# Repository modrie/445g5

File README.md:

# 445g5
ECE445 Group 5 Facilitated Instrument Learning

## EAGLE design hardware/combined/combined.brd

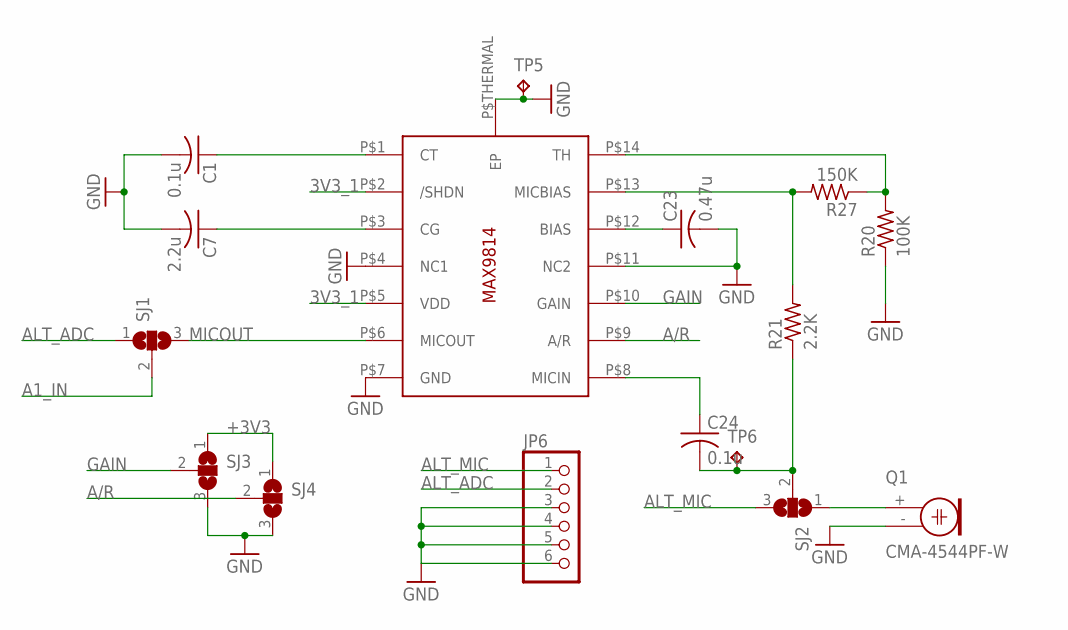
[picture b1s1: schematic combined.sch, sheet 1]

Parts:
C1, C24: 0.1u; C0603
C7: 2.2u; C0603
C23: 0.47u; C0603
JP6: PINHD-1X6; 1X06
Q1: CMA-4544PF-W; 9.7ELECTRET
R20: 100K; R0603
R21: 2.2K; R0603
R27: 150K; R0603
SJ1, SJ2, SJ3, SJ4: SJ2W; SJ_2
TP5, TP6: TPB1,27; B1,27
U$1: MAX9814TDFN14; TDFN14_3X3MM

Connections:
3V3_1: U$1.P$2 (/SHDN), U$1.P$5 (VDD)
+3V3: SJ3.1, SJ4.1; also elsewhere on the board
A1_IN: SJ1.2; also elsewhere on the board
A/R: SJ4.2, U$1.P$9 (A/R)
ALT_ADC: JP6.2, SJ1.1
ALT_MIC: JP6.1
GAIN: SJ3.2, U$1.P$10 (GAIN)
GND: C1.2, C7.2, C23.2, Q1.- (1), R20.1, SJ3.3, SJ4.3, TP5.TP, U$1.P$4 (NC1), U$1.P$7 (GND), U$1.P$11 (NC2), U$1.P$THERMAL (EP); also elsewhere on the board
INPUT: C24.2, R21.1, SJ2.2, TP6.TP
MICOUT: SJ1.3, U$1.P$6 (MICOUT)
unnamed: C24.1, U$1.P$8 (MICIN)
unnamed: C23.1, U$1.P$12 (BIAS)
unnamed: C1.1, U$1.P$1 (CT)
unnamed: C7.1, U$1.P$3 (CG)
unnamed: R20.2, R27.1, U$1.P$14 (TH)
unnamed: R21.2, R27.2, U$1.P$13 (MICBIAS)
unnamed: Q1.+ (2), SJ2.1
unnamed: JP6.3, JP6.4, JP6.5, JP6.6

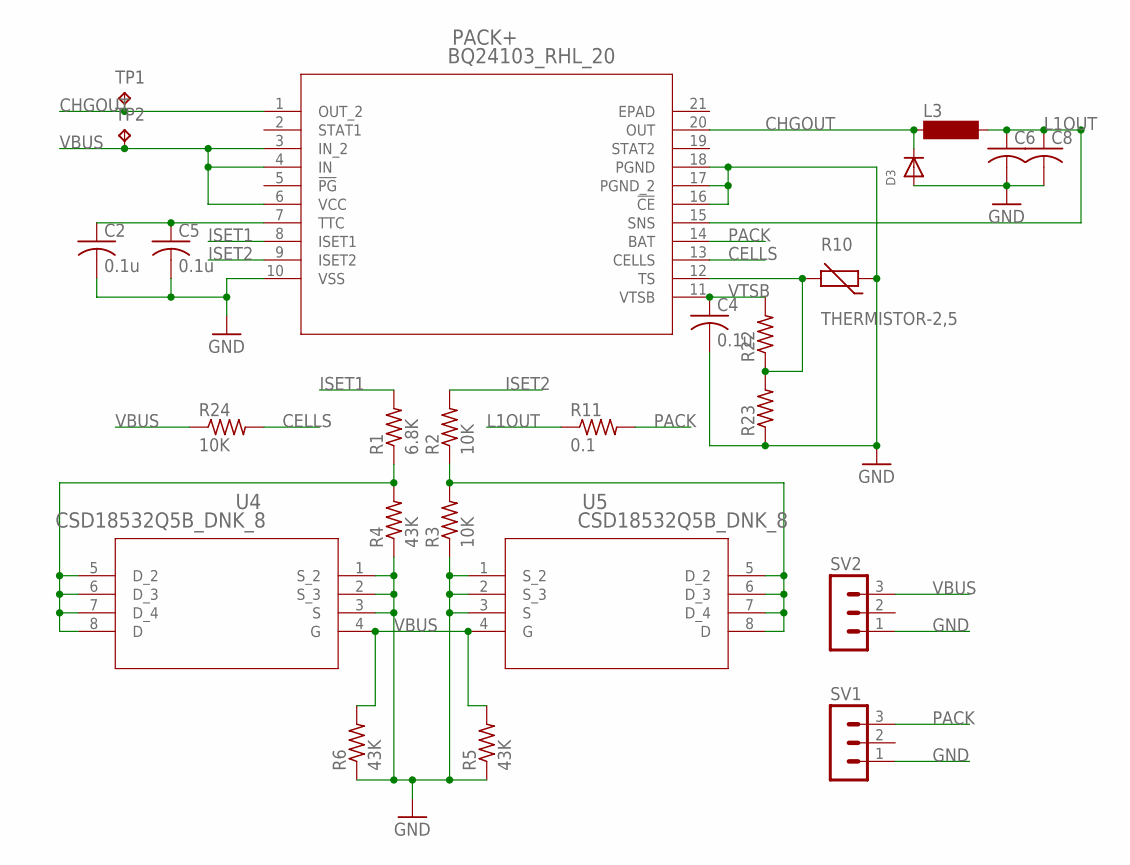
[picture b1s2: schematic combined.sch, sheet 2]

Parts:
C2, C4, C5: 0.1u; C0603
C6, C8: C-USC0805K; C0805K
D3: DIODESOD-323F; SOD-323F
L3: MS85
PACK+: BQ24103_RHL_20; RHL20_2P05X3P05
R1: 6.8K; R0603
R2, R3: 10K; R0603
R4, R5, R6: 43K; R0603
R10: THERMISTOR-2,5; RS-2,5
R11: 0.1; R0805
R22, R23: R-US_R0805; R0805
R24: 10K; R0805
SV1, SV2: MA03-1
TP1, TP2: TPB1,27; B1,27
U4, U5: CSD18532Q5B_DNK_8; DNK8

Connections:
CELLS: PACK+.13 (CELLS), R24.2
CHGOUT: D3.C, L3.1, PACK+.1 (OUT_2), PACK+.20 (OUT), TP1.TP
GND: C2.2, C4.2, C5.2, C6.2, C8.2, D3.A, PACK+.10 (VSS), PACK+.16 (!CE), PACK+.17 (PGND_2), PACK+.18 (PGND), R3.1, R4.1, R5.1, R6.1, R10.1, R23.1, SV1.1, SV2.1, U4.1 (S_2), U4.2 (S_3), U4.3 (S), U5.1 (S_2), U5.2 (S_3), U5.3 (S); also elsewhere on the board
ISET1: PACK+.8 (ISET1), R1.2
ISET2: PACK+.9 (ISET2), R2.2
L1OUT: C6.1, C8.1, L3.2, PACK+.15 (SNS), R11.1
unnamed: C2.1, C5.1, PACK+.7 (TTC)
unnamed: PACK+.12 (TS), R10.2, R22.1, R23.2
unnamed: R1.1, R4.2, U4.5 (D_2), U4.6 (D_3), U4.7 (D_4), U4.8 (D)
unnamed: R2.1, R3.2, U5.5 (D_2), U5.6 (D_3), U5.7 (D_4), U5.8 (D)
PACK: PACK+.14 (BAT), R11.2, SV1.3; also elsewhere on the board
VBUS: PACK+.3 (IN_2), PACK+.4 (IN), PACK+.6 (VCC), R5.2, R6.2, R24.1, SV2.3, TP2.TP, U4.4 (G), U5.4 (G); also elsewhere on the board
VTSB: C4.1, PACK+.11 (VTSB), R22.2

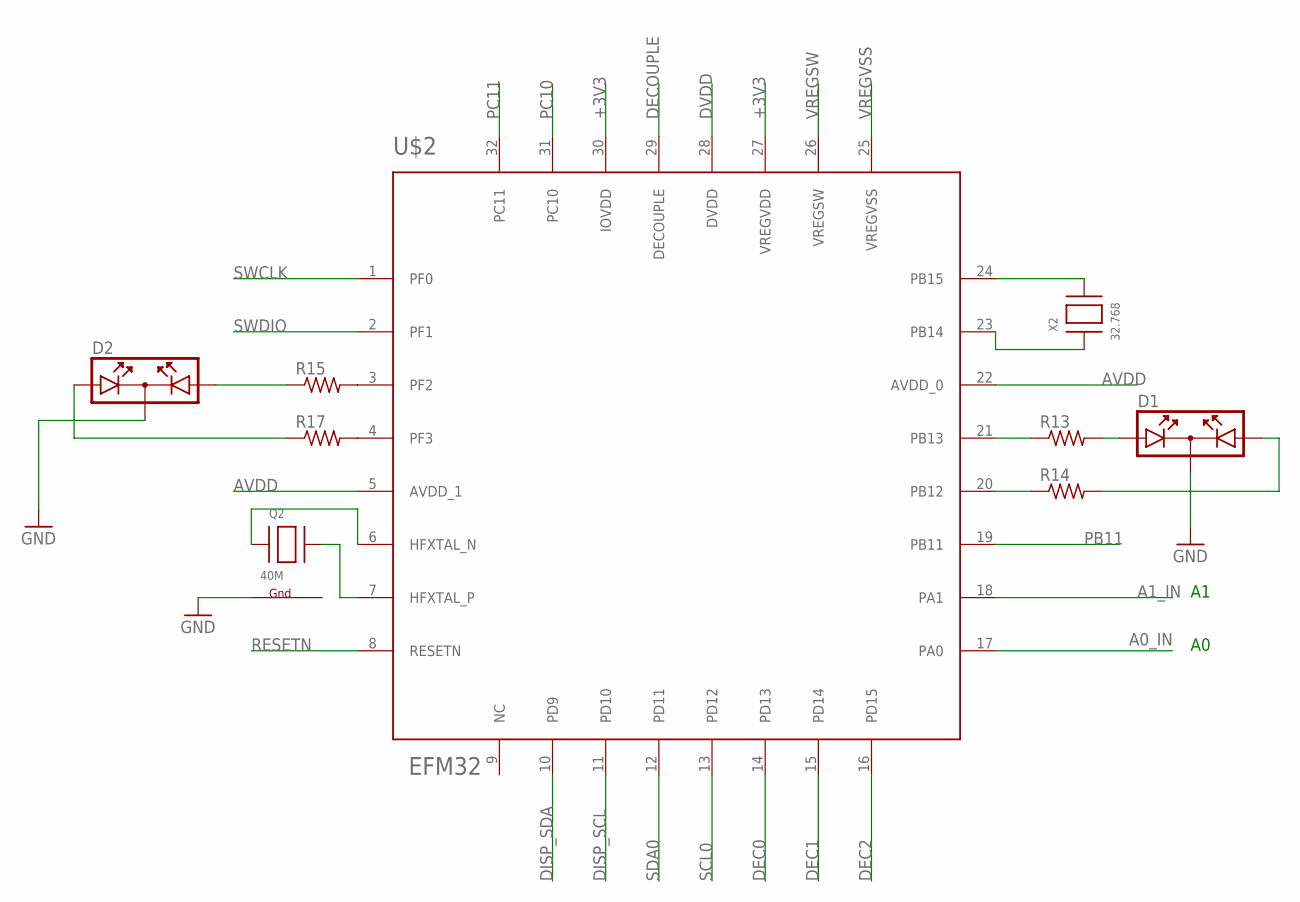
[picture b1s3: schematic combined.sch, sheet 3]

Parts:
D1, D2: DUOLED
Q2: 40M; NX3225
R13, R14, R15, R17: R-US_M0805; M0805
U$2: EFM32; QFN32
X2: 32.768; XTAL3215

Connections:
+3V3: U$2.27 (VREGVDD), U$2.30 (IOVDD); also elsewhere on the board
A0_IN: U$2.17 (PA0)
A1_IN: U$2.18 (PA1); also elsewhere on the board
AVDD: U$2.5 (AVDD_1), U$2.22 (AVDD_0); also elsewhere on the board
DEC0: U$2.14 (PD13); also elsewhere on the board
DEC1: U$2.15 (PD14); also elsewhere on the board
DEC2: U$2.16 (PD15); also elsewhere on the board
DECOUPLE: U$2.29 (DECOUPLE); also elsewhere on the board
DISP_SCL: U$2.11 (PD10); also elsewhere on the board
DISP_SDA: U$2.10 (PD9); also elsewhere on the board
DVDD: U$2.28 (DVDD); also elsewhere on the board
G2: Q2.2 (G2)
GND: D1.K, D2.K, Q2.4 (G1); also elsewhere on the board
unnamed: Q2.1 (X1), U$2.6 (HFXTAL_N)
unnamed: Q2.3 (X2), U$2.7 (HFXTAL_P)
unnamed: U$2.24 (PB15), X2.P$2
unnamed: U$2.23 (PB14), X2.P$1
unnamed: D1.A1, R13.2
unnamed: D1.A2, R14.2
unnamed: R15.2, U$2.3 (PF2)
unnamed: D2.A2, R15.1
unnamed: R17.2, U$2.4 (PF3)
unnamed: D2.A1, R17.1
unnamed: R14.1, U$2.20 (PB12)
unnamed: R13.1, U$2.21 (PB13)
PB11: U$2.19 (PB11); also elsewhere on the board
PC10: U$2.31 (PC10); also elsewhere on the board
PC11: U$2.32 (PC11); also elsewhere on the board
RESETN: U$2.8 (RESETN)
SCL0: U$2.13 (PD12); also elsewhere on the board
SDA0: U$2.12 (PD11); also elsewhere on the board
SWCLK: U$2.1 (PF0); also elsewhere on the board
SWDIO: U$2.2 (PF1); also elsewhere on the board
VREGSW: U$2.26 (VREGSW); also elsewhere on the board
VREGVSS: U$2.25 (VREGVSS)

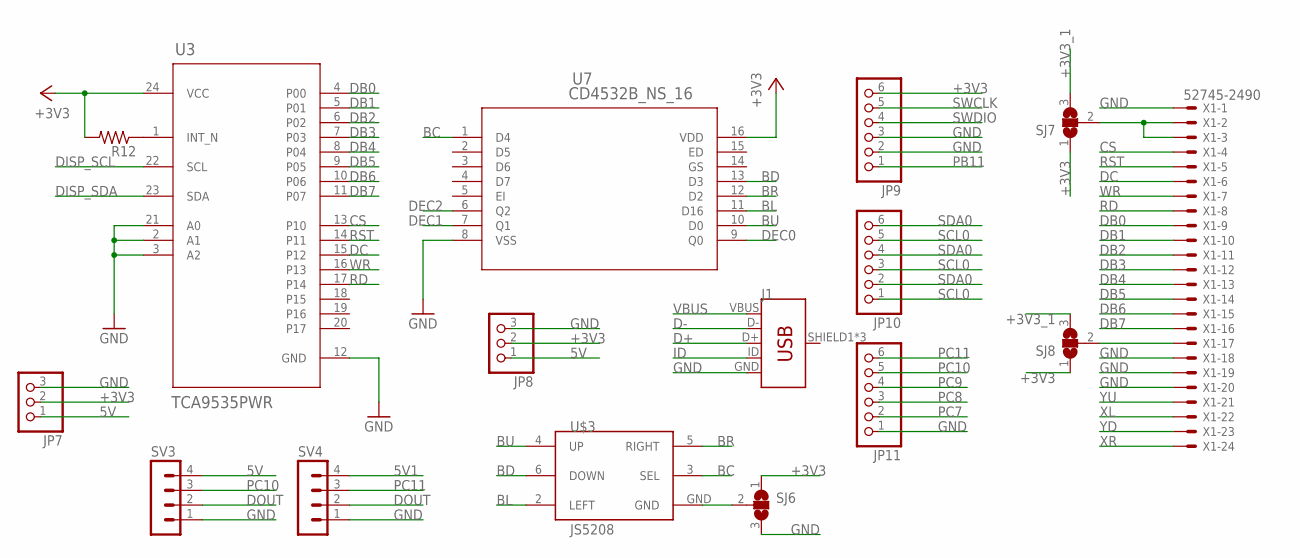
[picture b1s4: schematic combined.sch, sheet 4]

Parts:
J1: USB_MICRO-B_FEMALE-SMT; USB-B-MICRO-SMD
JP7, JP8: PINHD-1X3; 1X03
JP9, JP10, JP11: PINHD-1X6; 1X06
R12: R-US_M0805; M0805
SJ6, SJ7, SJ8: SJ2W; SJ_2
SV3, SV4: MA04-1
U3: TCA9535PWR; PW0024A_N
U7: CD4532B_NS_16; NS16
U$3: JS5208
X1: 52745-2490

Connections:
5V: JP7.1, JP8.1, SV3.4; also elsewhere on the board
5V1: SV4.4; also elsewhere on the board
+3V3: JP7.2, JP8.2, JP9.6, R12.2, SJ6.1, SJ7.1, SJ8.1, U3.24 (VCC), U7.16 (VDD); also elsewhere on the board
+3V3_1: SJ7.3, SJ8.3; also elsewhere on the board
BC: U7.1 (D4), U$3.3 (SEL)
BD: U7.13 (D3), U$3.6 (DOWN)
BL: U7.11 (D16), U$3.2 (LEFT)
BR: U7.12 (D2), U$3.5 (RIGHT)
BU: U7.10 (D0), U$3.4 (UP)
CS: U3.13 (P10), X1.4
D+: J1.D+
D-: J1.D-
DB0: U3.4 (P00), X1.9
DB1: U3.5 (P01), X1.10
DB2: U3.6 (P02), X1.11
DB3: U3.7 (P03), X1.12
DB4: U3.8 (P04), X1.13
DB5: U3.9 (P05), X1.14
DB6: U3.10 (P06), X1.15
DB7: U3.11 (P07), X1.16
DC: U3.15 (P12), X1.6
DEC0: U7.9 (Q0); also elsewhere on the board
DEC1: U7.7 (Q1); also elsewhere on the board
DEC2: U7.6 (Q2); also elsewhere on the board
DISP_SCL: U3.22 (SCL); also elsewhere on the board
DISP_SDA: U3.23 (SDA); also elsewhere on the board
DOUT: SV3.2, SV4.2
GND: J1.GND, JP7.3, JP8.3, JP9.2, JP9.3, JP11.1, SJ6.3, SV3.1, SV4.1, U3.2 (A1), U3.3 (A2), U3.12 (GND), U3.21 (A0), U7.8 (VSS), X1.1, X1.18, X1.19, X1.20; also elsewhere on the board
ID: J1.ID
unnamed: SJ7.2, X1.2, X1.3
unnamed: SJ8.2, X1.17
unnamed: SJ6.2, U$3.GND
unnamed: R12.1, U3.1 (INT_N)
PB11: JP9.1; also elsewhere on the board
PC7: JP11.2
PC8: JP11.3
PC9: JP11.4
PC10: JP11.5, SV3.3; also elsewhere on the board
PC11: JP11.6, SV4.3; also elsewhere on the board
RD: U3.17 (P14), X1.8
RST: U3.14 (P11), X1.5
SCL0: JP10.1, JP10.3, JP10.5; also elsewhere on the board
SDA0: JP10.2, JP10.4, JP10.6; also elsewhere on the board
SWCLK: JP9.5; also elsewhere on the board
SWDIO: JP9.4; also elsewhere on the board
VBUS: J1.VBUS; also elsewhere on the board
WR: U3.16 (P13), X1.7
XL: X1.22
XR: X1.24
YD: X1.23
YU: X1.21

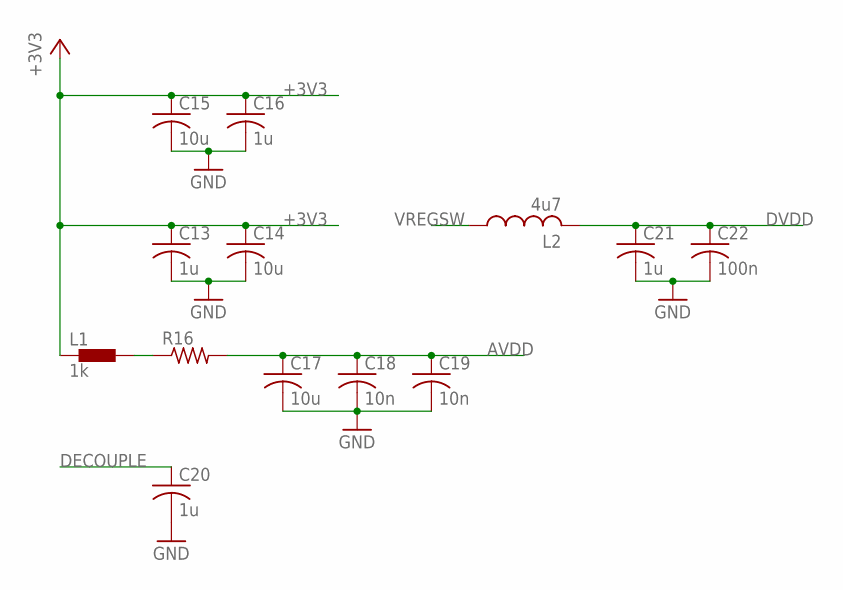
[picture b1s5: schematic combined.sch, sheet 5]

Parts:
C13, C16, C20, C21: 1u; C0805
C14, C15, C17: 10u; C0805
C18, C19: 10n; C0805
C22: 100n; C0805
L1: 1k; 0402
L2: 4u7; L3225P
R16: R-US_R0603; R0603

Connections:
+3V3: C13.1, C14.1, C15.1, C16.1, L1.1; also elsewhere on the board
AVDD: C17.1, C18.1, C19.1, R16.2; also elsewhere on the board
DECOUPLE: C20.1; also elsewhere on the board
DVDD: C21.1, C22.1, L2.2; also elsewhere on the board
GND: C13.2, C14.2, C15.2, C16.2, C17.2, C18.2, C19.2, C20.2, C21.2, C22.2; also elsewhere on the board
unnamed: L1.2, R16.1
VREGSW: L2.1; also elsewhere on the board

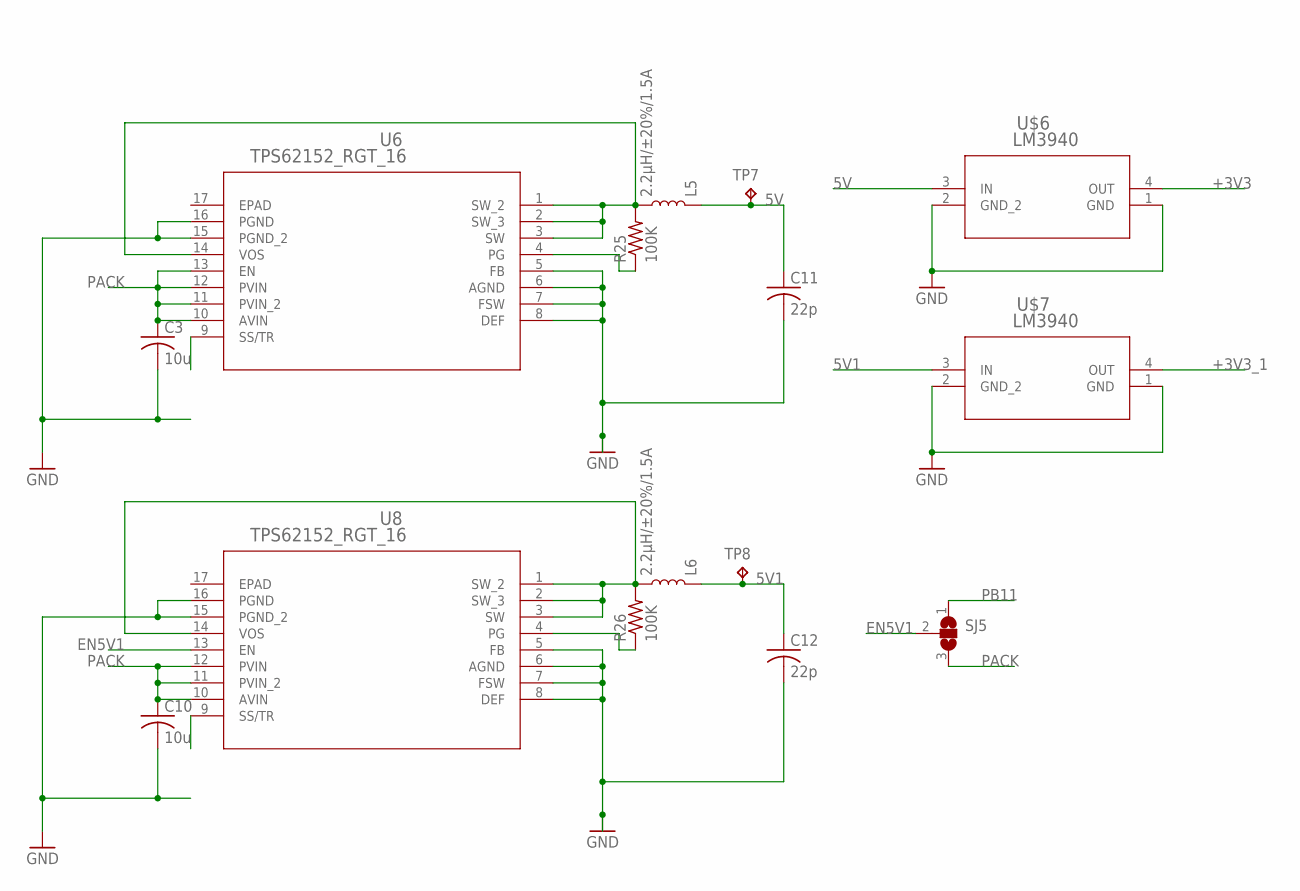
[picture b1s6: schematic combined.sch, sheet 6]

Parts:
C3, C10: 10u; C0603K
C11, C12: 22p; C0603K
L5, L6: 2.2µH/±20%/1.5A; INDUCTOR_2.2UH
R25, R26: 100K; R0603
SJ5: SJ2W; SJ_2
TP7, TP8: TPB1,27; B1,27
U6, U8: TPS62152_RGT_16; RGT16_1P7X1P7
U$6, U$7: LM3940; MP04A

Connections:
5V: C11.1, L5.P$1 (1), TP7.TP, U$6.3 (IN); also elsewhere on the board
5V1: C12.1, L6.P$1 (1), TP8.TP, U$7.3 (IN); also elsewhere on the board
+3V3: U$6.4 (OUT); also elsewhere on the board
+3V3_1: U$7.4 (OUT); also elsewhere on the board
EN5V1: SJ5.2, U8.13 (EN)
GND: C3.2, C10.2, C11.2, C12.2, U6.5 (FB), U6.6 (AGND), U6.7 (FSW), U6.8 (DEF), U6.15 (PGND_2), U6.16 (PGND), U8.5 (FB), U8.6 (AGND), U8.7 (FSW), U8.8 (DEF), U8.15 (PGND_2), U8.16 (PGND), U$6.1 (GND), U$6.2 (GND_2), U$7.1 (GND), U$7.2 (GND_2); also elsewhere on the board
unnamed: L5.P$2 (2), R25.2, U6.1 (SW_2), U6.2 (SW_3), U6.3 (SW), U6.14 (VOS)
unnamed: R25.1, U6.4 (PG)
unnamed: L6.P$2 (2), R26.2, U8.1 (SW_2), U8.2 (SW_3), U8.3 (SW), U8.14 (VOS)
unnamed: R26.1, U8.4 (PG)
PACK: C3.1, C10.1, SJ5.3, U6.10 (AVIN), U6.11 (PVIN_2), U6.12 (PVIN), U6.13 (EN), U8.10 (AVIN), U8.11 (PVIN_2), U8.12 (PVIN); also elsewhere on the board
PB11: SJ5.1; also elsewhere on the board

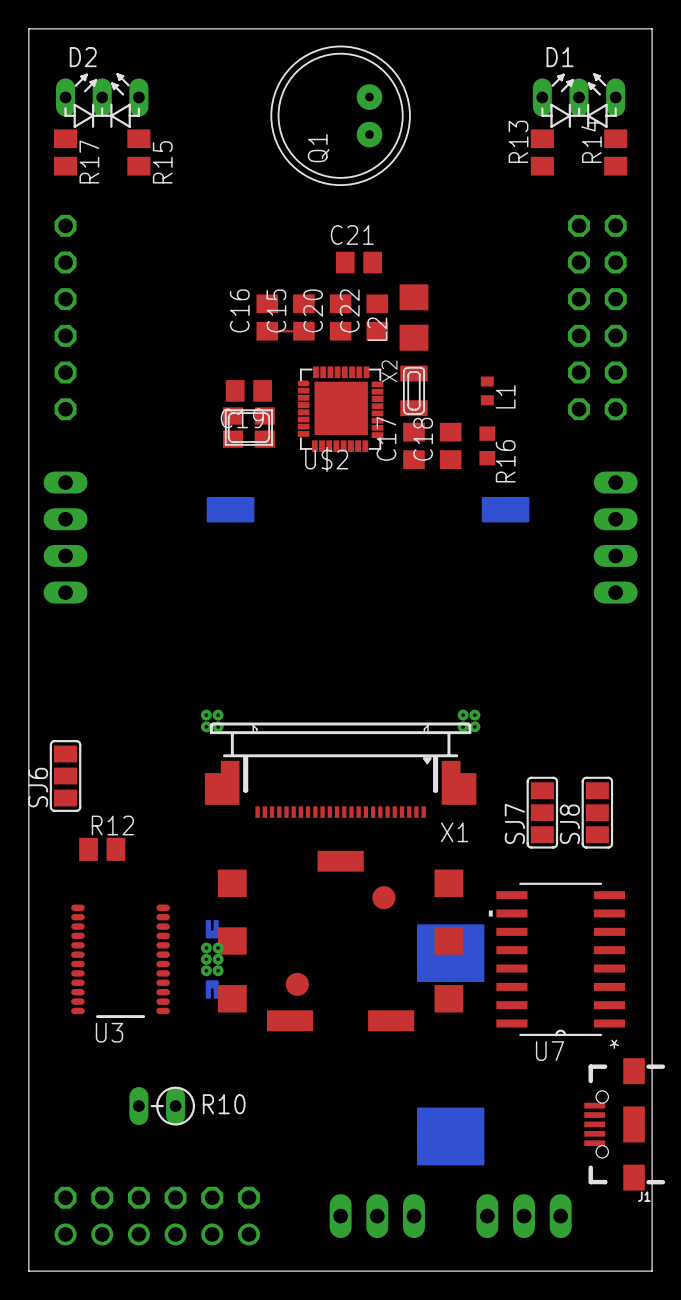
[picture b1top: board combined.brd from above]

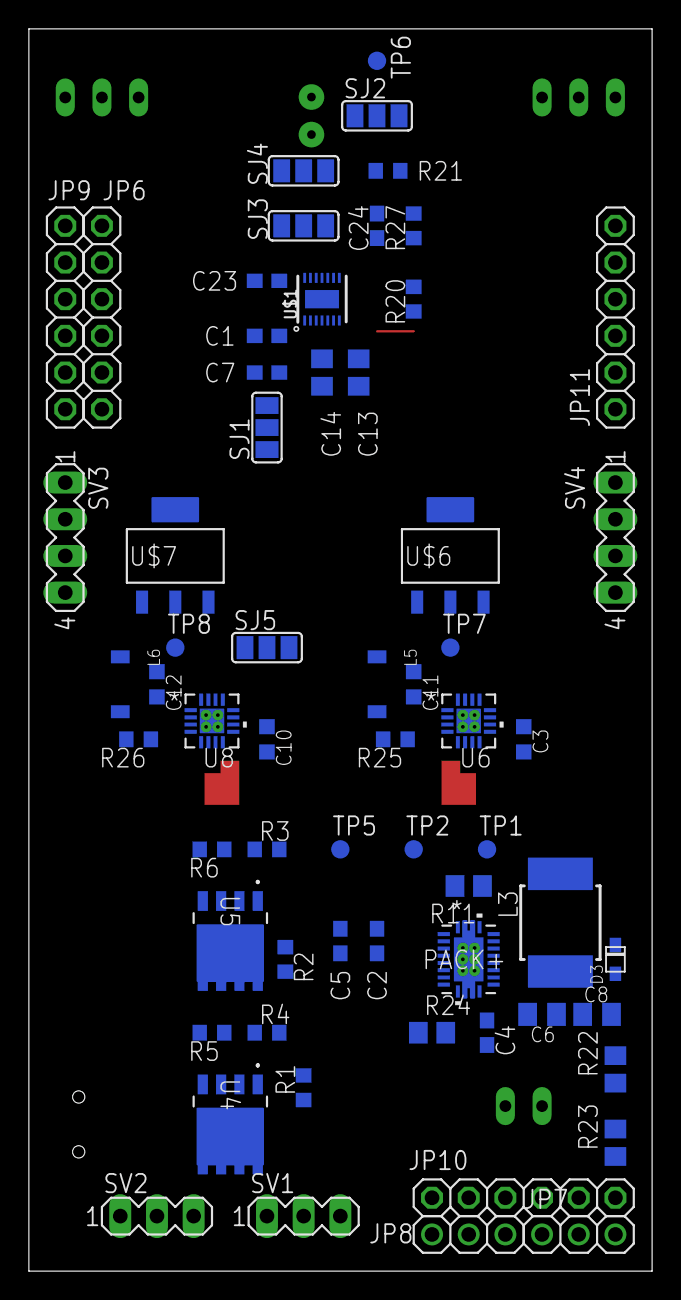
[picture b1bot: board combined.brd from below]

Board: 2 copper layers, 43.2 x 86.0 mm, 94 parts (63 on the bottom side), 89 nets.

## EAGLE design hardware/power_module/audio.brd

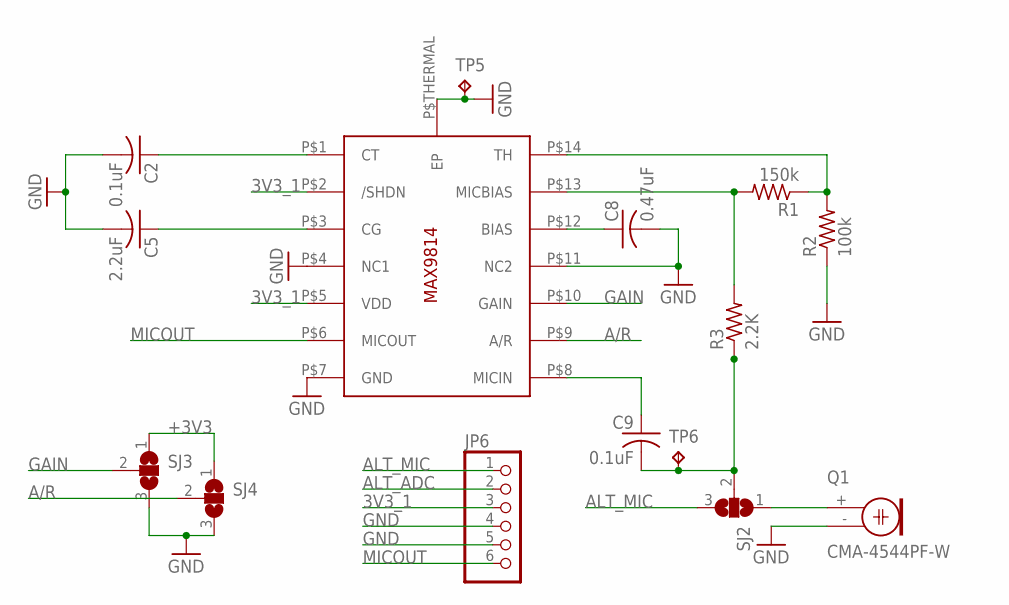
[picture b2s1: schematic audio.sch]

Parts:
C2, C9: 0.1uF; C0805K
C5: 2.2uF; C0805K
C8: 0.47uF; C0805K
JP6: PINHD-1X6; 1X06
Q1: CMA-4544PF-W; 9.7ELECTRET
R1: 150k; R0805
R2: 100k; R0805
R3: 2.2K; R0805
SJ2, SJ3, SJ4: SJ2W; SJ_2
TP5, TP6: TPB1,27; B1,27
U$1: MAX9814TDFN14; TDFN14_3X3MM

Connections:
3V3_1: JP6.3, U$1.P$2 (/SHDN), U$1.P$5 (VDD)
+3V3: SJ3.1, SJ4.1
A/R: SJ4.2, U$1.P$9 (A/R)
ALT_ADC: JP6.2
ALT_MIC: JP6.1, SJ2.3
GAIN: SJ3.2, U$1.P$10 (GAIN)
GND: C2.2, C5.2, C8.2, JP6.4, JP6.5, Q1.- (1), R2.1, SJ3.3, SJ4.3, TP5.TP, U$1.P$4 (NC1), U$1.P$7 (GND), U$1.P$11 (NC2), U$1.P$THERMAL (EP)
INPUT: C9.2, R3.1, SJ2.2, TP6.TP
MICOUT: JP6.6, U$1.P$6 (MICOUT)
unnamed: C9.1, U$1.P$8 (MICIN)
unnamed: C8.1, U$1.P$12 (BIAS)
unnamed: C2.1, U$1.P$1 (CT)
unnamed: C5.1, U$1.P$3 (CG)
unnamed: R1.1, R2.2, U$1.P$14 (TH)
unnamed: R1.2, R3.2, U$1.P$13 (MICBIAS)
unnamed: Q1.+ (2), SJ2.1

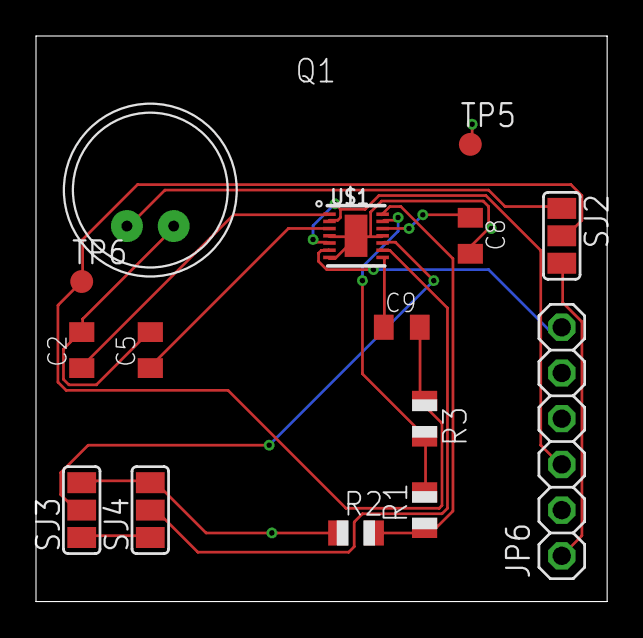
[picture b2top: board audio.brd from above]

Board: 2 copper layers, 31.7 x 31.4 mm, 15 parts (0 on the bottom side), 15 nets.

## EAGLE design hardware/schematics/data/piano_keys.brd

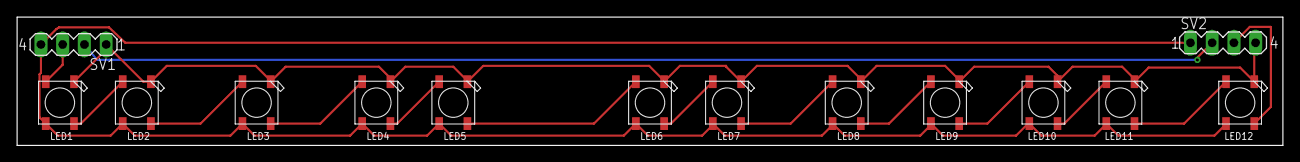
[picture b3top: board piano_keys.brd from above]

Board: 2 copper layers, 148.0 x 15.0 mm, 14 parts (0 on the bottom side), 16 nets.

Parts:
LED1, LED2, LED3, LED4, LED5, LED6, LED7, LED8, LED9, LED10, LED11, LED12: WS2812B5050; WS2812B
SV1, SV2: MA04-1

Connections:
5V1: LED1.1-VDD, LED2.1-VDD, LED3.1-VDD, LED4.1-VDD, LED5.1-VDD, LED6.1-VDD, LED7.1-VDD, LED8.1-VDD, LED9.1-VDD, LED10.1-VDD, LED11.1-VDD, LED12.1-VDD, SV1.4, SV2.1
DIN: LED1.4-DIN, SV1.3
DIN_1: SV1.2, SV2.2
DOUT_1: LED12.2-DOUT, SV2.3
GND: LED1.3-GND, LED2.3-GND, LED3.3-GND, LED4.3-GND, LED5.3-GND, LED6.3-GND, LED7.3-GND, LED8.3-GND, LED9.3-GND, LED10.3-GND, LED11.3-GND, LED12.3-GND, SV1.1, SV2.4
unnamed: LED3.2-DOUT, LED4.4-DIN
unnamed: LED4.2-DOUT, LED5.4-DIN
unnamed: LED5.2-DOUT, LED6.4-DIN
unnamed: LED6.2-DOUT, LED7.4-DIN
unnamed: LED7.2-DOUT, LED8.4-DIN
unnamed: LED8.2-DOUT, LED9.4-DIN
unnamed: LED9.2-DOUT, LED10.4-DIN
unnamed: LED10.2-DOUT, LED11.4-DIN
unnamed: LED11.2-DOUT, LED12.4-DIN
unnamed: LED1.2-DOUT, LED2.4-DIN
unnamed: LED2.2-DOUT, LED3.4-DIN

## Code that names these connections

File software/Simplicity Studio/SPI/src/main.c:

/**************************************************************************//**
 * @main_series1.c
 * @brief Demonstrates USART1 as SPI master.
 * @version 0.0.1
 ******************************************************************************
 * @section License
 * <b>Copyright 2015 Silicon Labs, Inc. http://www.silabs.com</b>
 *******************************************************************************
 *
 * This file is licensed under the Silabs License Agreement. See the file
 * "Silabs_License_Agreement.txt" for details. Before using this software for
 * any purpose, you must agree to the terms of that agreement.
 *
 ******************************************************************************/

#include "em_device.h"
#include "em_chip.h"
#include "em_cmu.h"
#include "em_gpio.h"
#include "em_usart.h"
#include "retargetswo.h"
#include <stdint.h>
#include <stdio.h>


#define NUM_LEDS 		 24
const uint8_t two_bits_to_SPI[4] = {0x88 ,0xE8, 0x8E,0xEE};
// Lookup table for bytes
// Index - 0b(MSB)(LSB)
// MSB is sent to line first, so the values corresponding to the index are flipped

// e.g  Sending 0b10
//			0 -> 0b1000 = 0x8
//			1 -> 0b1110 = 0xE
// 		Index is 2 so lookup table returns 0x8E in correct order



volatile uint32_t msTicks; /* counts 1ms timeTicks */

void Delay(uint32_t dlyTicks);

/***************************************************************************//**
 * @brief SysTick_Handler
 * Interrupt Service Routine for system tick counter
 ******************************************************************************/
void SysTick_Handler(void)
{
  msTicks++;       /* increment counter necessary in Delay()*/
}

/***************************************************************************//**
 * @brief Delays number of msTick Systicks (typically 1 ms)
 * @param dlyTicks Number of ticks to delay
 ******************************************************************************/
void Delay(uint32_t dlyTicks)
{
  uint32_t curTicks;

  curTicks = msTicks;
  while ((msTicks - curTicks) < dlyTicks) ;
}


/**************************************************************************//**
 * @brief Initialize USART1
 *****************************************************************************/
void initUSART1 (void)
{
	CMU_ClockEnable(cmuClock_HFPER, true);
	CMU_ClockEnable(cmuClock_GPIO, true);
	CMU_ClockEnable(cmuClock_USART1, true);

	// Start with default config, then modify as necessary
	USART_InitSync_TypeDef config = USART_INITSYNC_DEFAULT;
	config.master       = true;            // master mode
	config.baudrate     = 3333333; //5000000;         // CLK freq is 1 MHz
	config.autoCsEnable = true;            // CS pin controlled by hardware, not firmware
	config.clockMode    = usartClockMode0; // clock idle low, sample on rising/first edge
	config.msbf         = true;            // send MSB first
    USART_InitSync(USART1, &config);

    // Set USART pin locations
    USART1->ROUTELOC0 = (USART_ROUTELOC0_CLKLOC_LOC15) | // US1_CLK† † † †on location 15 = PD9
                        (USART_ROUTELOC0_CSLOC_LOC15)  | // US1_CS† † † † on location 15 = PD10
                        (USART_ROUTELOC0_TXLOC_LOC15)  | // US1_TX (MOSI) on location 15 = PC10
                        (USART_ROUTELOC0_RXLOC_LOC15);   // US1_RX (MISO) on location 15 = PC11

    // Enable USART pins
    USART1->ROUTEPEN = USART_ROUTEPEN_CLKPEN | USART_ROUTEPEN_CSPEN | USART_ROUTEPEN_TXPEN | USART_ROUTEPEN_RXPEN;

    // Configure GPIO mode
    GPIO_PinModeSet(gpioPortD, 9, gpioModePushPull, 1); // US1_CLK is push pull
    GPIO_PinModeSet(gpioPortD, 10, gpioModePushPull, 1); // US1_CS is push pull
    GPIO_PinModeSet(gpioPortC, 10, gpioModePushPull, 1); // US1_TX (MOSI) is push pull
    GPIO_PinModeSet(gpioPortC, 11, gpioModeInput, 1);    // US1_RX (MISO) is input

    // Clear RX buffer and shift register
    USART1->CMD |= USART_CMD_CLEARRX;

    // Clear TX buffer and shift register
    USART1->CMD |= USART_CMD_CLEARTX;

    // Enable USART1
    USART_Enable(USART1, usartEnable);
}



void spi_illuminate(uint8_t r, uint8_t g, uint8_t b){

	// send green
	for (int i = 0; i <= 3 ; i++){
		g <<= i*2;
		USART_Tx(USART1, two_bits_to_SPI[(g & 192U) >> 6]);  // bit mask with 11000000 and shift, then index into bits_to_SPI array
	}

	// send red
	for (int i = 0; i <= 3 ; i++){
		r <<= i*2;
		USART_Tx(USART1, two_bits_to_SPI[(r & 192U)>>6]);   // bit mask with 11000000 and shift, then index into bits_to_SPI array
	}


	// send blue
	for (int i = 0; i <= 3 ; i++){
		b <<= i*2;
		USART_Tx(USART1, two_bits_to_SPI[(b & 192U) >> 6]); // bit mask with 11000000 and shift, then index into bits_to_SPI array
	}
}


void LEDs_latch(void){
	// Pull line down for LEDs to latch
	// 20 *  300 ns = ~ 6 microsecond line
	for(int i = 0; i < 20; i++){
		USART_Tx(USART1, 0x00);
	}
}


void light_LEDs(bool* LEDs){

	for (int i = 0; i < NUM_LEDS ; i++){
		if (LEDs[i] == true){
			spi_illuminate( 0, 3, 3);
		}
		else{
			spi_illuminate( 0, 0, 0);
		}
	}

	LEDs_latch();
}



/**************************************************************************//**
 * @brief Main function
 *****************************************************************************/


int main(void)
{
  // Initialize chip
  CHIP_Init();

  // Initialize USART1 as SPI slave
  initUSART1();


  /* Setup SysTick Timer for 1 msec interrupts  */
  if (SysTick_Config(CMU_ClockFreqGet(cmuClock_CORE) / 1000)) {
    while (1) ;
  }


  bool LEDs[NUM_LEDS] = {true, false, true, false, true, false, true, false, true, false, true, false,
		  true, false, true, false, true, false, true, false, true, false, true, false};

  while(1){
	  light_LEDs(LEDs);
	  Delay(1000);
	  for (int i = 0 ; i <= NUM_LEDS; i++){
		  LEDs[i] = !LEDs[i];
	  }
  }

}

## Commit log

2018-02-15 added the multi-pitch detection thesis
2018-02-15 moved some stuff around
2018-02-15 EFM32 doc and transcription thesis
2018-02-17 piano_keys.sch, QFM32.sch, and data_comm.sch
2018-02-18 adding the mic and amplifier schematic
2018-02-18 adding the software component
2018-02-19 updated test.ipynb
2018-02-21 add dev board schematic
2018-02-22 power
2018-02-22 updated qfm32 schematic with i2c lines and mic in
2018-02-23 Yin Algorithm Source
2018-02-26 ipynb for non-negative matrix factrization algorithm
2018-02-26 Added recordings
2018-02-28 add nmf in python
2018-03-03 16k file and added load_wav
2018-03-03 added load_wav
2018-03-03 adding add_noise function and noisy audios
2018-03-05 updated noisy audio files
2018-03-06 working on real time.
2018-03-06 add audio unit datasheet
2018-03-08 real time + NMF
2018-03-11 Decoupled listener object from algorithm
2018-03-12 working on real time yin
2018-03-15 TCA9535PWR JS5208 libraries
2018-03-21 monophonic latency ~3 ms'
2018-03-29 board everything
2018-03-29 piano keys schematic and board
2018-03-29 adjusted key distances
2018-03-29 piano keys
2018-03-29 final board 1
2018-03-29 cleanup
2018-04-10 polyphonic algorithm
2018-04-10 okok
2018-04-12 yin algorithm on MCU
2018-04-18 working programmable LEDs, in progress i2c display
2018-04-19 on board led works
2018-04-21 polyphonic in C , working on post FFT debugging
2018-04-22 adding example file
2018-04-22 working polyphonic in c
    a
2018-04-22 polyphonic c working with 240 bytes
2018-04-23 hardcoded triangle filters
2018-04-23 reduced ram usage
2018-04-23 added f0CandsFreqBinStart_Flash
